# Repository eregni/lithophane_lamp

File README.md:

# Lithophane lamp
Program to control a 3d printed lithophane rgb lamp.  
3d model source: https://www.thingiverse.com/thing:1370792  

It works with an arduino pro mini and sk9822 rgb leds

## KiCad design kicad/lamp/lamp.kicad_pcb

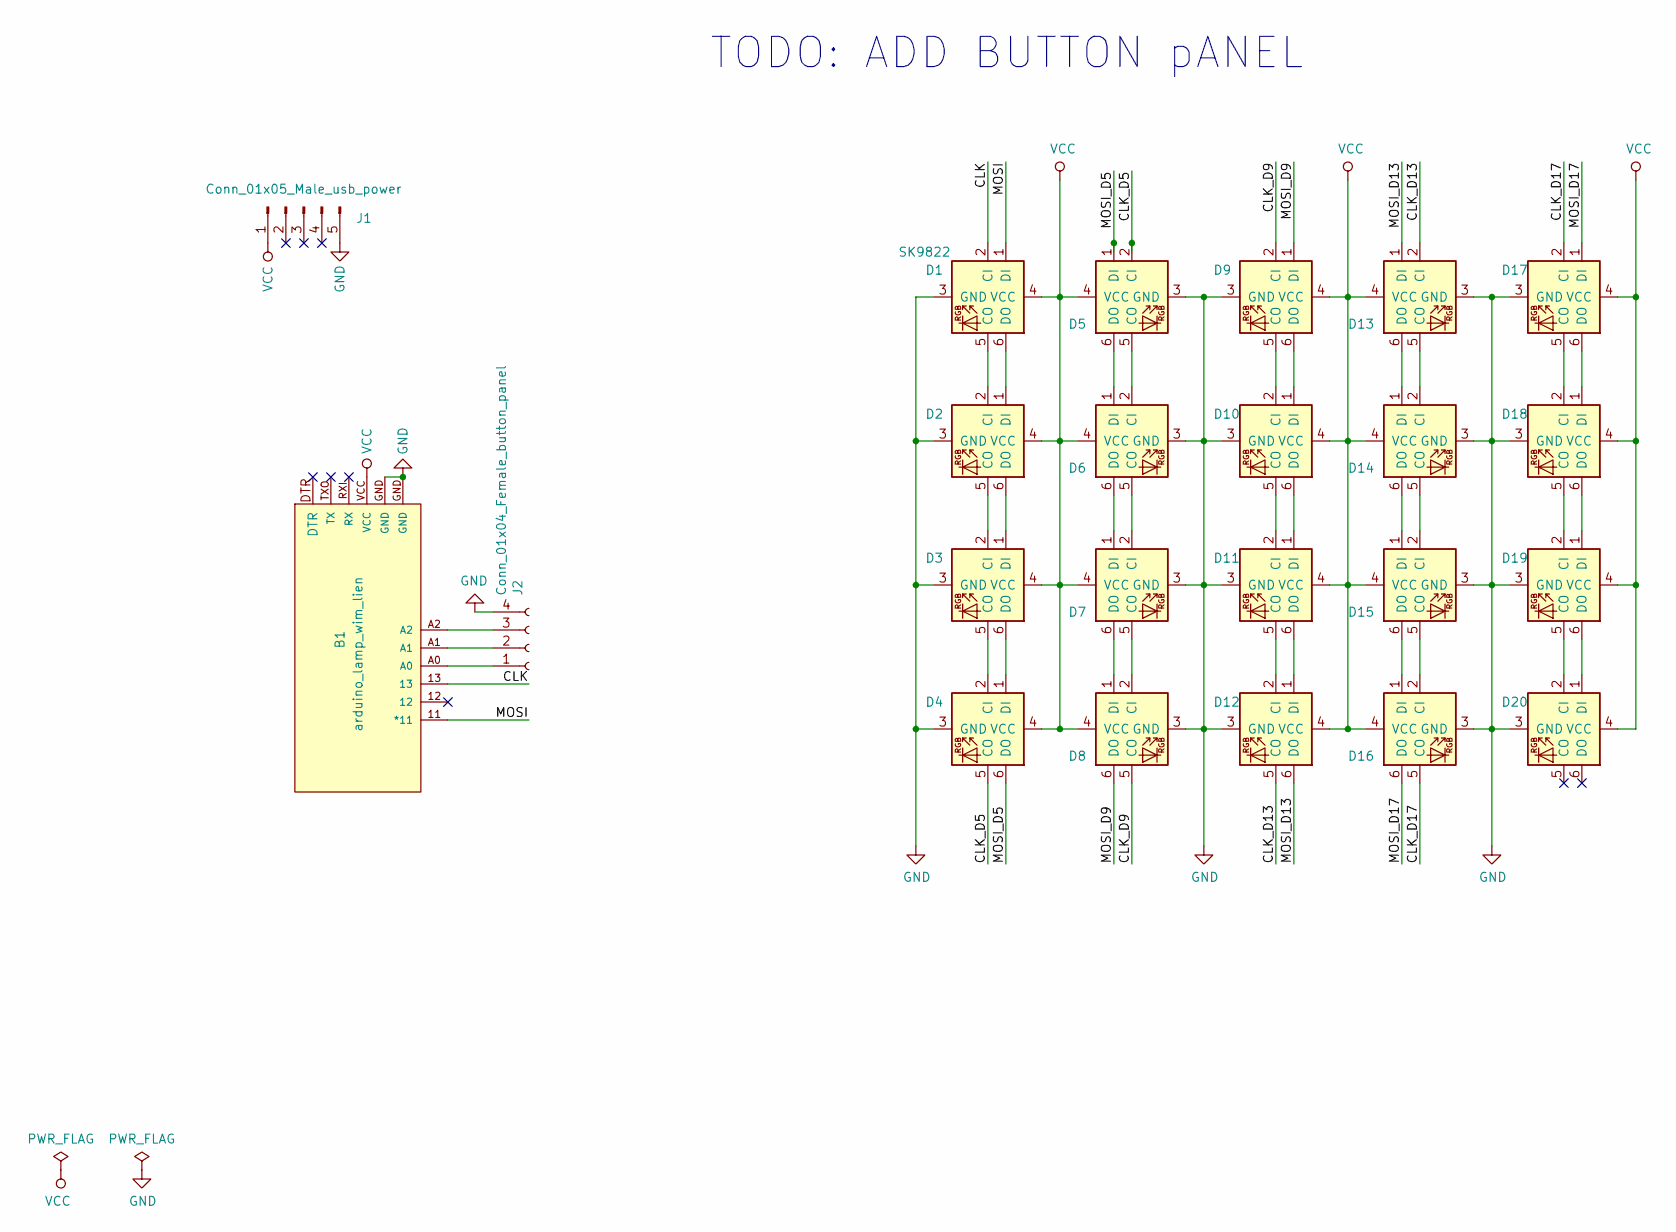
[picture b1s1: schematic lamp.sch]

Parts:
B1: arduino_lamp_wim_lien; ARDUINO_LAMP_WIM_LIEN
D1, D2, D3, D4, D5, D6, D7, D8, D9, D10, D11, D12, D13, D14, D15, D16, D17, D18, D19, D20: SK9822; LED_WS2812_PLCC6_5.0x5.0mm_P1.6mm
J1: Conn_01x05_Male_usb_power; PinHeader_1x05_P2.54mm_Vertical
J2: Conn_01x04_Female_button_panel; JST_XH_B4B-XH-A_1x04_P2.50mm_Vertical

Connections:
/CLK: B1.13, D1.2 (CI)
/CLK_D5: D4.5 (CO), D5.2 (CI)
/CLK_D9: D8.5 (CO), D9.2 (CI)
/CLK_D13: D12.5 (CO), D13.2 (CI)
/CLK_D17: D16.5 (CO), D17.2 (CI)
/MOSI: B1.11 (*11), D1.1 (DI)
/MOSI_D5: D4.6 (DO), D5.1 (DI)
/MOSI_D9: D8.6 (DO), D9.1 (DI)
/MOSI_D13: D12.6 (DO), D13.1 (DI)
/MOSI_D17: D16.6 (DO), D17.1 (DI)
GND: B1.GND, D1.3 (GND), D2.3 (GND), D3.3 (GND), D4.3 (GND), D5.3 (GND), D6.3 (GND), D7.3 (GND), D8.3 (GND), D9.3 (GND), D10.3 (GND), D11.3 (GND), D12.3 (GND), D13.3 (GND), D14.3 (GND), D15.3 (GND), D16.3 (GND), D17.3 (GND), D18.3 (GND), D19.3 (GND), D20.3 (GND), J1.5, J2.4
unnamed: B1.A0, J2.1
unnamed: B1.A1, J2.2
unnamed: B1.A2, J2.3
unnamed: D1.5 (CO), D2.2 (CI)
unnamed: D1.6 (DO), D2.1 (DI)
unnamed: D2.5 (CO), D3.2 (CI)
unnamed: D2.6 (DO), D3.1 (DI)
unnamed: D3.5 (CO), D4.2 (CI)
unnamed: D3.6 (DO), D4.1 (DI)
unnamed: D5.5 (CO), D6.2 (CI)
unnamed: D5.6 (DO), D6.1 (DI)
unnamed: D6.5 (CO), D7.2 (CI)
unnamed: D6.6 (DO), D7.1 (DI)
unnamed: D7.5 (CO), D8.2 (CI)
unnamed: D7.6 (DO), D8.1 (DI)
unnamed: D9.6 (DO), D10.1 (DI)
unnamed: D9.5 (CO), D10.2 (CI)
unnamed: D10.5 (CO), D11.2 (CI)
unnamed: D10.6 (DO), D11.1 (DI)
unnamed: D11.5 (CO), D12.2 (CI)
unnamed: D11.6 (DO), D12.1 (DI)
unnamed: D13.5 (CO), D14.2 (CI)
unnamed: D13.6 (DO), D14.1 (DI)
unnamed: D14.5 (CO), D15.2 (CI)
unnamed: D14.6 (DO), D15.1 (DI)
unnamed: D15.5 (CO), D16.2 (CI)
unnamed: D15.6 (DO), D16.1 (DI)
unnamed: D17.5 (CO), D18.2 (CI)
unnamed: D17.6 (DO), D18.1 (DI)
unnamed: D18.5 (CO), D19.2 (CI)
unnamed: D18.6 (DO), D19.1 (DI)
unnamed: D19.5 (CO), D20.2 (CI)
unnamed: D19.6 (DO), D20.1 (DI)
VCC: B1.VCC, D1.4 (VCC), D2.4 (VCC), D3.4 (VCC), D4.4 (VCC), D5.4 (VCC), D6.4 (VCC), D7.4 (VCC), D8.4 (VCC), D9.4 (VCC), D10.4 (VCC), D11.4 (VCC), D12.4 (VCC), D13.4 (VCC), D14.4 (VCC), D15.4 (VCC), D16.4 (VCC), D17.4 (VCC), D18.4 (VCC), D19.4 (VCC), D20.4 (VCC), J1.1

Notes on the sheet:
TODO: ADD BUTTON pANEL

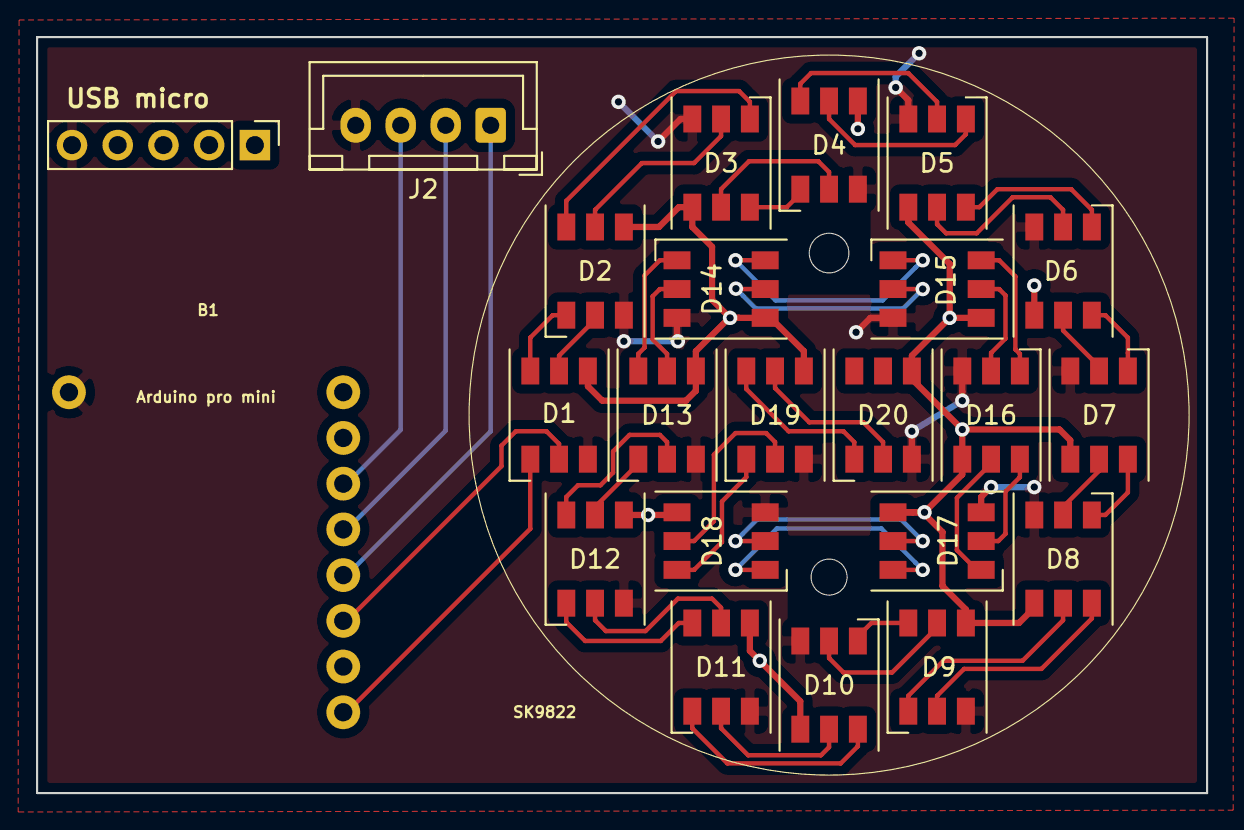
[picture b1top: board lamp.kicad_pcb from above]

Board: 2 copper layers, 65.0 x 42.0 mm, 23 parts (0 on the bottom side), 45 nets.
